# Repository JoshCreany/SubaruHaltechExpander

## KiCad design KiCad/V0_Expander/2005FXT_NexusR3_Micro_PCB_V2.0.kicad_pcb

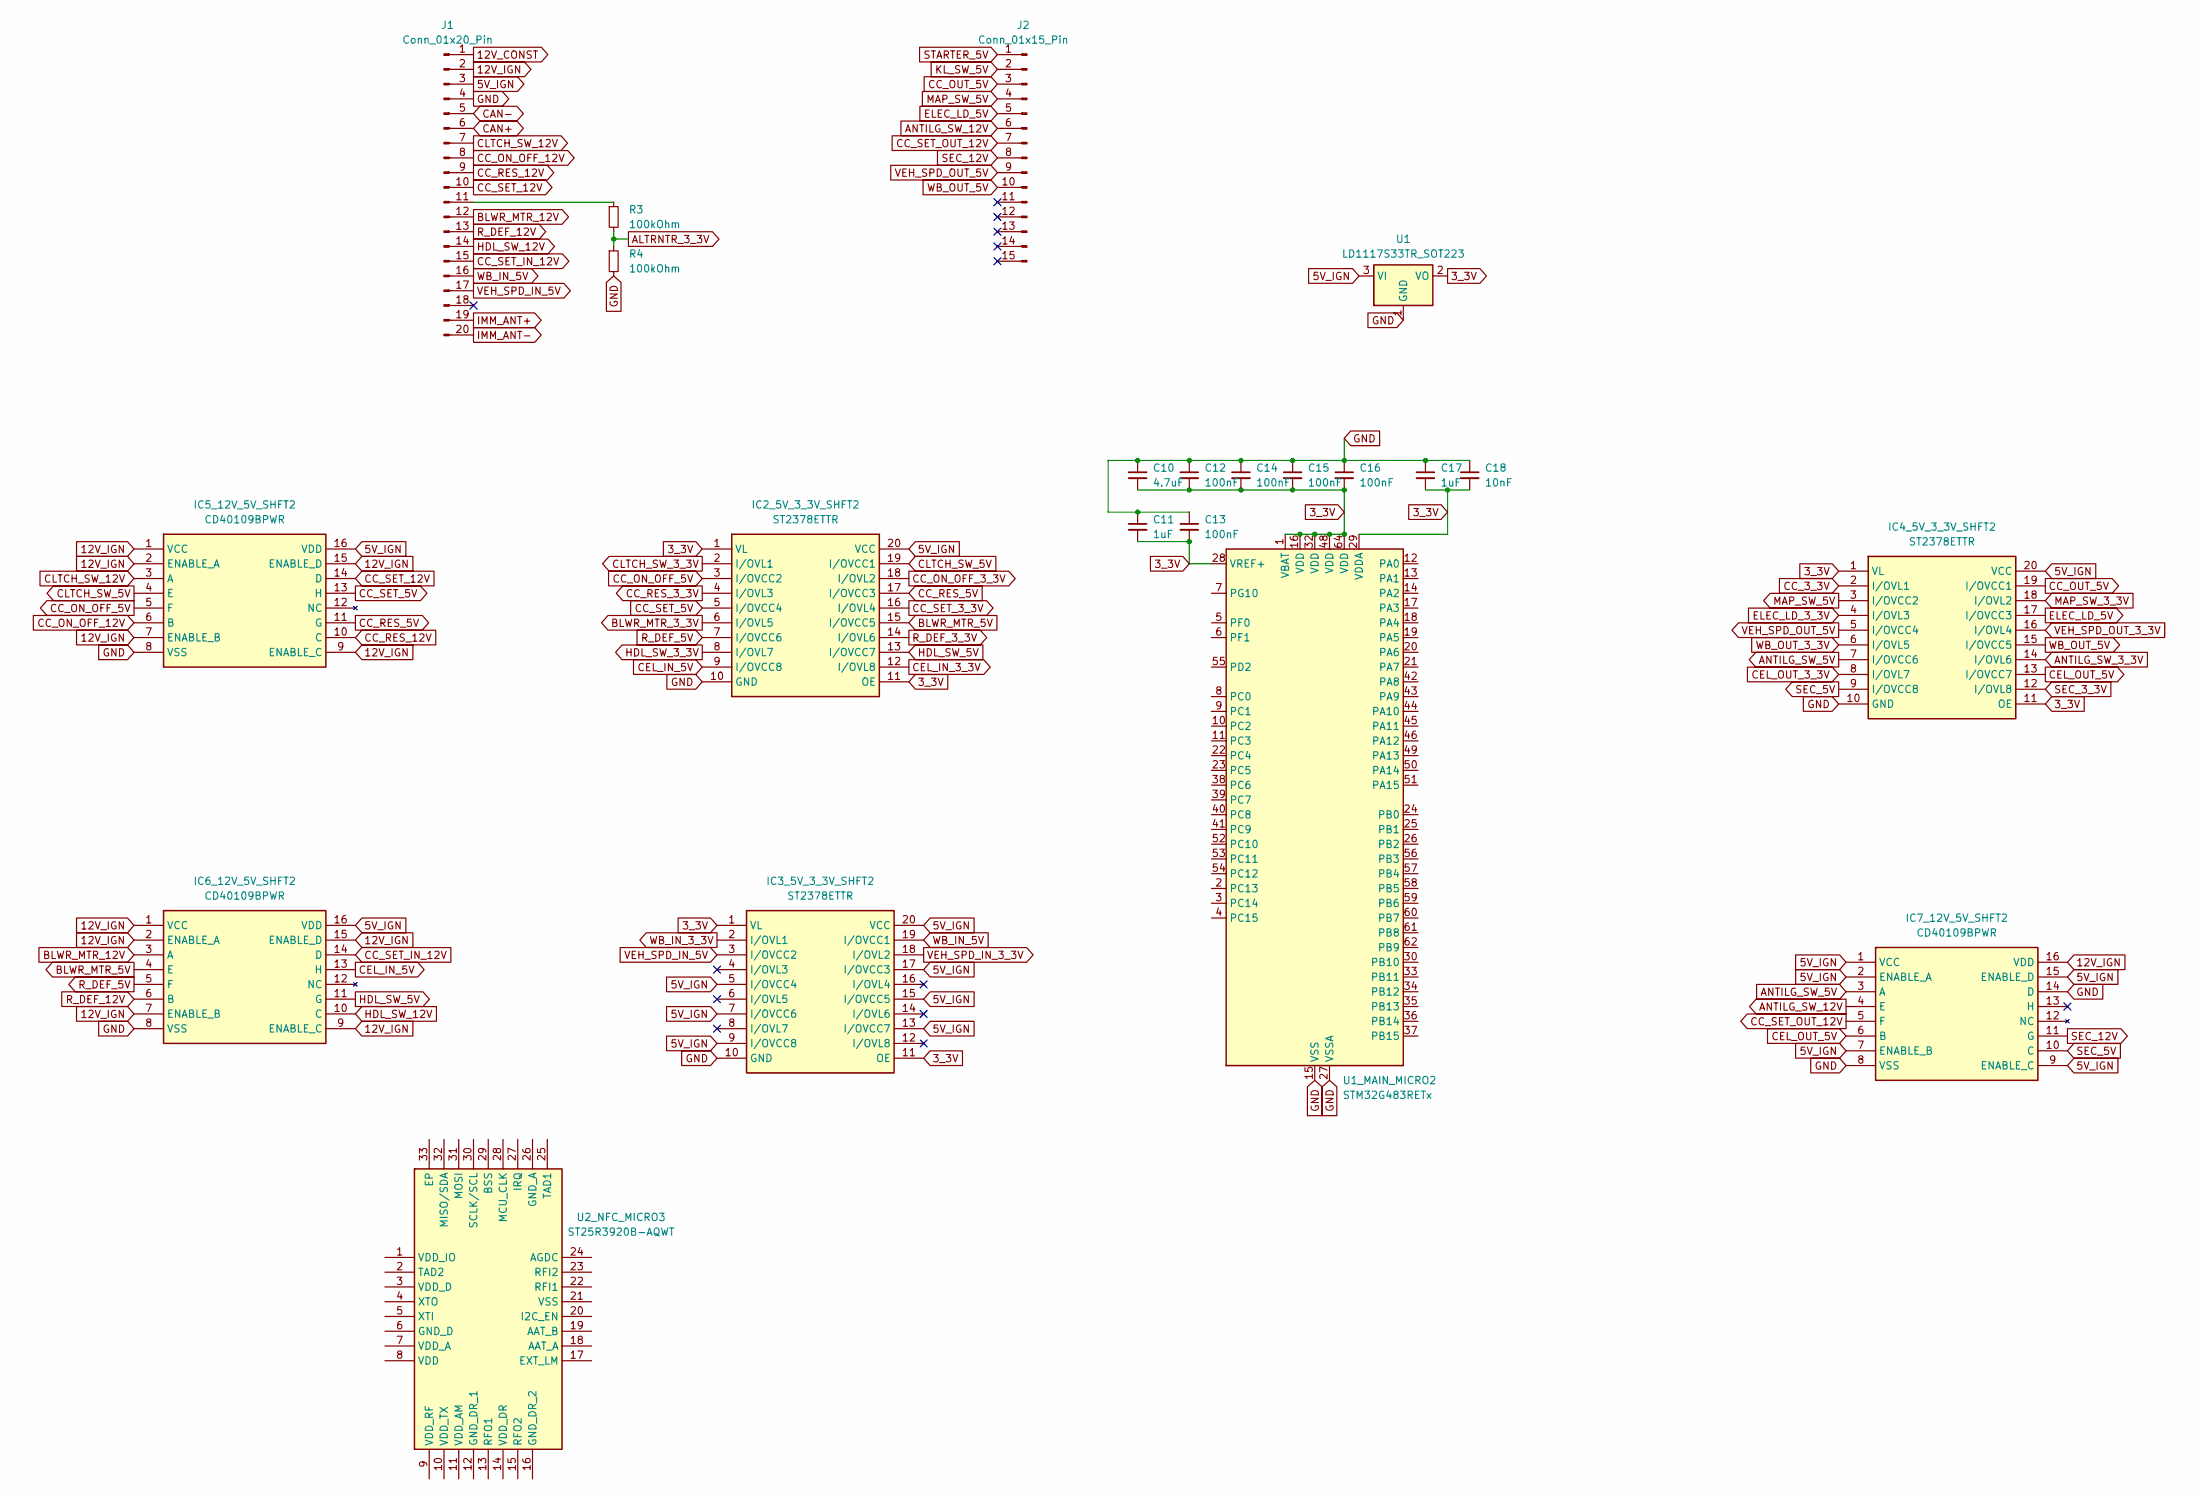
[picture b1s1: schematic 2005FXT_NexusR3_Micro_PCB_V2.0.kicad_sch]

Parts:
C10: 4.7uF; C_0805_2012Metric
C11, C17: 1uF; C_0805_2012Metric
C12, C13, C14, C15, C16: 100nF; C_0805_2012Metric
C18: 10nF; C_0805_2012Metric
IC2_5V_3_3V_SHFT2, IC3_5V_3_3V_SHFT2, IC4_5V_3_3V_SHFT2: ST2378ETTR; SOP65P640X120-20N; Manufacturer_Part_Number ST2378ETTR; Mouser Part Number 511-ST2378ET
IC5_12V_5V_SHFT2, IC6_12V_5V_SHFT2, IC7_12V_5V_SHFT2: CD40109BPWR; SOP65P640X120-16N; Mouser Part Number 595-CD40109BPWR
J1: Conn_01x20_Pin; PinHeader_1x20_P2.54mm_Vertical
J2: Conn_01x15_Pin; PinHeader_1x15_P2.54mm_Vertical
R3, R4: 100kOhm; R_0805_2012Metric
U1: LD1117S33TR_SOT223; SOT-223-3_TabPin2
U1_MAIN_MICRO2: STM32G483RETx; LQFP-64_10x10mm_P0.5mm
U2_NFC_MICRO3: ST25R3920B-AQWT; ST25R3920BAQWT; Manufacturer_Part_Number ST25R3920B-AQWT; Mouser Part Number 511-ST25R3920B-AQWT

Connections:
/MICRO_ALTRNTR: J1.11, R3.1
MICRO_3_3V: C10.2, C11.2, C12.2, C13.2, C14.2, C15.2, C16.2, C17.2, C18.2, IC2_5V_3_3V_SHFT2.1 (VL), IC2_5V_3_3V_SHFT2.11 (OE), IC3_5V_3_3V_SHFT2.1 (VL), IC3_5V_3_3V_SHFT2.11 (OE), IC4_5V_3_3V_SHFT2.1 (VL), IC4_5V_3_3V_SHFT2.11 (OE), U1.2 (VO), U1_MAIN_MICRO2.1 (VBAT), U1_MAIN_MICRO2.16 (VDD), U1_MAIN_MICRO2.28 (VREF+), U1_MAIN_MICRO2.29 (VDDA), U1_MAIN_MICRO2.32 (VDD), U1_MAIN_MICRO2.48 (VDD), U1_MAIN_MICRO2.64 (VDD)
MICRO_5V: IC2_5V_3_3V_SHFT2.20 (VCC), IC3_5V_3_3V_SHFT2.5 (I/OVCC4), IC3_5V_3_3V_SHFT2.7 (I/OVCC6), IC3_5V_3_3V_SHFT2.9 (I/OVCC8), IC3_5V_3_3V_SHFT2.13 (I/OVCC7), IC3_5V_3_3V_SHFT2.15 (I/OVCC5), IC3_5V_3_3V_SHFT2.17 (I/OVCC3), IC3_5V_3_3V_SHFT2.20 (VCC), IC4_5V_3_3V_SHFT2.20 (VCC), IC5_12V_5V_SHFT2.16 (VDD), IC6_12V_5V_SHFT2.16 (VDD), IC7_12V_5V_SHFT2.1 (VCC), IC7_12V_5V_SHFT2.2 (ENABLE_A), IC7_12V_5V_SHFT2.7 (ENABLE_B), IC7_12V_5V_SHFT2.9 (ENABLE_C), IC7_12V_5V_SHFT2.15 (ENABLE_D), J1.3, U1.3 (VI)
MICRO_12V_IGN: IC5_12V_5V_SHFT2.1 (VCC), IC5_12V_5V_SHFT2.2 (ENABLE_A), IC5_12V_5V_SHFT2.7 (ENABLE_B), IC5_12V_5V_SHFT2.9 (ENABLE_C), IC5_12V_5V_SHFT2.15 (ENABLE_D), IC6_12V_5V_SHFT2.1 (VCC), IC6_12V_5V_SHFT2.2 (ENABLE_A), IC6_12V_5V_SHFT2.7 (ENABLE_B), IC6_12V_5V_SHFT2.9 (ENABLE_C), IC6_12V_5V_SHFT2.15 (ENABLE_D), IC7_12V_5V_SHFT2.16 (VDD), J1.2
MICRO_ALTRNTR_3_3V: R3.2, R4.1
MICRO_ANTILG_SW_3_3V: IC4_5V_3_3V_SHFT2.14 (I/OVL6)
MICRO_ANTILG_SW_5V: IC4_5V_3_3V_SHFT2.7 (I/OVCC6), IC7_12V_5V_SHFT2.3 (A)
MICRO_ANTILG_SW_12V: IC7_12V_5V_SHFT2.4 (E), J2.6
MICRO_BLWR_MTR_3_3V: IC2_5V_3_3V_SHFT2.6 (I/OVL5)
MICRO_BLWR_MTR_5V: IC2_5V_3_3V_SHFT2.15 (I/OVCC5), IC6_12V_5V_SHFT2.4 (E)
MICRO_BLWR_MTR_12V: IC6_12V_5V_SHFT2.3 (A), J1.12
MICRO_CC_3_3V: IC4_5V_3_3V_SHFT2.2 (I/OVL1)
MICRO_CC_5V: IC4_5V_3_3V_SHFT2.19 (I/OVCC1), J2.3
MICRO_CC_ON_OFF_3_3V: IC2_5V_3_3V_SHFT2.18 (I/OVL2)
MICRO_CC_ON_OFF_5V: IC2_5V_3_3V_SHFT2.3 (I/OVCC2), IC5_12V_5V_SHFT2.5 (F)
MICRO_CC_ON_OFF_12V: IC5_12V_5V_SHFT2.6 (B), J1.8
MICRO_CC_RES_3_3V: IC2_5V_3_3V_SHFT2.4 (I/OVL3)
MICRO_CC_RES_5V: IC2_5V_3_3V_SHFT2.17 (I/OVCC3), IC5_12V_5V_SHFT2.11 (G)
MICRO_CC_RES_12V: IC5_12V_5V_SHFT2.10 (C), J1.9
MICRO_CC_SET_3_3V: IC2_5V_3_3V_SHFT2.16 (I/OVL4)
MICRO_CC_SET_5V: IC2_5V_3_3V_SHFT2.5 (I/OVCC4), IC5_12V_5V_SHFT2.13 (H)
MICRO_CC_SET_12V: IC5_12V_5V_SHFT2.14 (D), J1.10
MICRO_CEL_IN_3_3V: IC2_5V_3_3V_SHFT2.12 (I/OVL8)
MICRO_CEL_IN_5V: IC2_5V_3_3V_SHFT2.9 (I/OVCC8), IC6_12V_5V_SHFT2.13 (H)
MICRO_CEL_IN_12V: IC6_12V_5V_SHFT2.14 (D), J1.15
MICRO_CEL_OUT_3_3V: IC4_5V_3_3V_SHFT2.8 (I/OVL7)
MICRO_CEL_OUT_5V: IC4_5V_3_3V_SHFT2.13 (I/OVCC7), IC7_12V_5V_SHFT2.6 (B)
MICRO_CEL_OUT_12V: IC7_12V_5V_SHFT2.5 (F), J2.7
MICRO_CLTCH_SW_3_3V: IC2_5V_3_3V_SHFT2.2 (I/OVL1)
MICRO_CLTCH_SW_5V: IC2_5V_3_3V_SHFT2.19 (I/OVCC1), IC5_12V_5V_SHFT2.4 (E)
MICRO_CLTCH_SW_12V: IC5_12V_5V_SHFT2.3 (A), J1.7
MICRO_ELEC_LD_3_3V: IC4_5V_3_3V_SHFT2.4 (I/OVL3)
MICRO_ELEC_LD_5V: IC4_5V_3_3V_SHFT2.17 (I/OVCC3), J2.5
MICRO_GND: C10.1, C11.1, C12.1, C13.1, C14.1, C15.1, C16.1, C17.1, C18.1, IC2_5V_3_3V_SHFT2.10 (GND), IC3_5V_3_3V_SHFT2.10 (GND), IC4_5V_3_3V_SHFT2.10 (GND), IC5_12V_5V_SHFT2.8 (VSS), IC6_12V_5V_SHFT2.8 (VSS), IC7_12V_5V_SHFT2.8 (VSS), IC7_12V_5V_SHFT2.14 (D), J1.4, R4.2, U1.1 (GND), U1_MAIN_MICRO2.15 (VSS), U1_MAIN_MICRO2.27 (VSSA), U1_MAIN_MICRO2.31 (VSS), U1_MAIN_MICRO2.47 (VSS), U1_MAIN_MICRO2.63 (VSS)
MICRO_HDL_SW_3_3V: IC2_5V_3_3V_SHFT2.8 (I/OVL7)
MICRO_HDL_SW_5V: IC2_5V_3_3V_SHFT2.13 (I/OVCC7), IC6_12V_5V_SHFT2.11 (G)
MICRO_HDL_SW_12V: IC6_12V_5V_SHFT2.10 (C), J1.14
MICRO_MAP_SW_3_3V: IC4_5V_3_3V_SHFT2.18 (I/OVL2)
MICRO_MAP_SW_5V: IC4_5V_3_3V_SHFT2.3 (I/OVCC2), J2.4
MICRO_R_DEF_3_3V: IC2_5V_3_3V_SHFT2.14 (I/OVL6)
MICRO_R_DEF_5V: IC2_5V_3_3V_SHFT2.7 (I/OVCC6), IC6_12V_5V_SHFT2.5 (F)
MICRO_R_DEF_12V: IC6_12V_5V_SHFT2.6 (B), J1.13
MICRO_SEC_3_3V: IC4_5V_3_3V_SHFT2.12 (I/OVL8)
MICRO_SEC_5V: IC4_5V_3_3V_SHFT2.9 (I/OVCC8), IC7_12V_5V_SHFT2.10 (C)
MICRO_SEC_12V: IC7_12V_5V_SHFT2.11 (G), J2.8
MICRO_VEH_SPD_IN_3_3V: IC3_5V_3_3V_SHFT2.18 (I/OVL2)
MICRO_VEH_SPD_IN_5V: IC3_5V_3_3V_SHFT2.3 (I/OVCC2), J1.17
MICRO_VEH_SPD_OUT_3_3V: IC4_5V_3_3V_SHFT2.16 (I/OVL4)
MICRO_VEH_SPD_OUT_5V: IC4_5V_3_3V_SHFT2.5 (I/OVCC4), J2.9
MICRO_WB_IN_3_3V: IC3_5V_3_3V_SHFT2.2 (I/OVL1)
MICRO_WB_IN_5V: IC3_5V_3_3V_SHFT2.19 (I/OVCC1), J1.16
MICRO_WB_OUT_3_3V: IC4_5V_3_3V_SHFT2.6 (I/OVL5)
MICRO_WB_OUT_5V: IC4_5V_3_3V_SHFT2.15 (I/OVCC5), J2.10

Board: 4 copper layers, 20 parts (0 on the bottom side), 16 nets, no tracks yet.

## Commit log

2026-01-20 First button press is registering
